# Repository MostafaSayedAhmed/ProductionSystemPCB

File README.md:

# Production System PCB
Internship final project for Embedded system track internship offered by Egypt Makes Electronics company
## Desciption
### 1- Prerequisites
Design a system that simulates a production process in a factory using the following
hardware:
• Two microcontrollers.
• LCD
• Keypad
• Temperature Sensor
• LDR Sensor
• Fan
### 2- System Description:

Design a multi-function machine that can do the following using modes with only one
switch to switch between the modes of operation.
To Enter the operation mode, the user must Enter his password first [1,2,3,4]
Then using a single switch, the user can switch between the following modes as follow:
The first press on the switch → will go to Mode A
The second press on the switch → will go to mode B
The third press on the switch → will go to mode B
<dl>
  <dt>Mode A: ‘Calculator’</dt>
  <ds>
On Microcontroller 1: ‘
Implement a calculator, Numbers should be from 0 to 9, and the operation is (+ -
\* / )
Display on the first MCU LCD.
</ds>
  <dt>Mode B: ‘Alarm System’</dt>
<ds>On Microcontroller 1:
User need an alarm system for a server room, A led toggle every 1 sec “flashing”,
and the value of the temp. sensor control the flashing of the led.
<ul>
<li> if the value increased than 50c:
  <ul>
    <li>
 The led will be flash every 100msec, buzzer will on and off every
100 msec
    </li>
    <li>
Send Signal to Microcontroller 2 to move the motor in CW
direction with maximum speed. Using any communication
protocol (i.e. UART)
  </li>
  </ul>
  </li>
<li>
 If the value is lower than 50c:
  <ul>
  <li>
The led will be flash every 1 sec, buzzer and motor are turned
off.
</li>
  <li>
 Send Signal to Microcontroller 2 to move the motor in CCW
direction with half speed. Using any communication protocol
(i.e. UART)
On Microcontroller 2:
Controller the motor speed according to the received signal

</li>
</li>
</ul></ul>
</ds>
<dt>Mode C: ‘Sun light indication’ </dt>
<ds>
  On Microcontroller 2
<ul>
<li>if LDR detect the high amount of light:
The Led will turned off and the second MCU will send txt to be print on
LCD “Morning” of the first MCU through UART. </li>
  <li>if LDR detect the Low amount of light:
The led will turned on and the second MCU will send txt to be print on LCD
“Night” of the first MCU through UART.</li>
</ul>
</ds>
</dt>

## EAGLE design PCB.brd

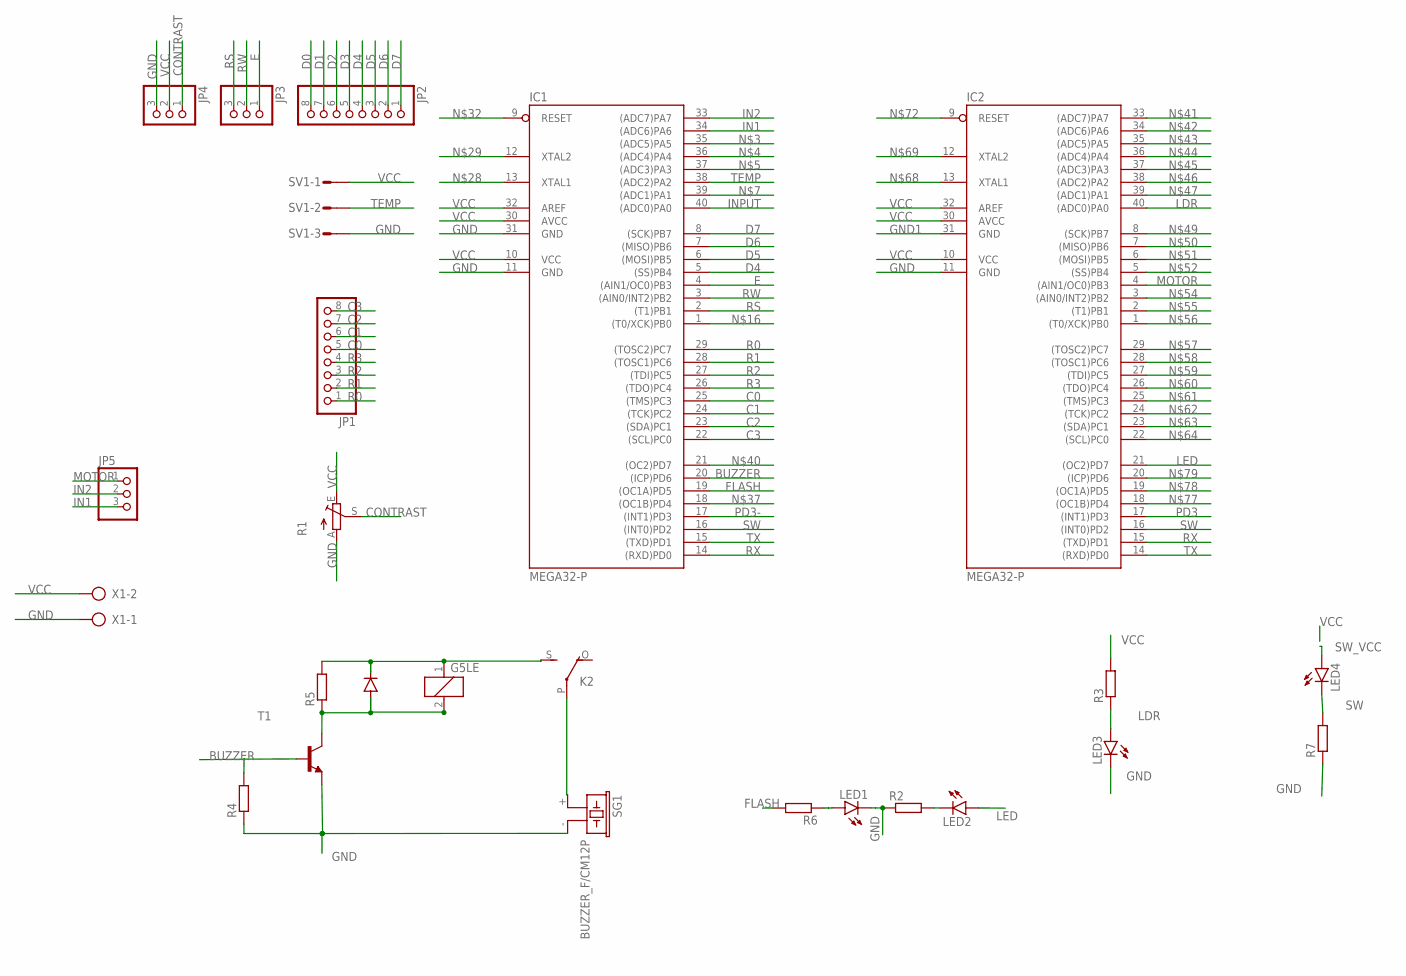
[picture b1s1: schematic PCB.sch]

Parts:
D1: 1N4004; DO41-10
IC1, IC2: MEGA32-P; DIL40
JP1, JP2: PINHD-1X8; 1X08
JP3, JP4, JP5: PINHD-1X3; 1X03
K2: G5LE
LED1, LED2: LED3MM
LED3, LED4: LED5MM
R1: TRIM_EU-RJ9W; RJ9W
R2, R3, R4, R5, R6, R7: R-EU_0204/7; 0204/7
SG1: BUZZER_F/CM12P
SV1: CON-AMP-MT_S03P
T1: 2N2222-NPN-TO92-EBC; TO92-EBC
X1: CON-PTR500_AK300/2

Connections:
BUZZER: IC1.20 ((ICP)PD6)
C0: IC1.25 ((TMS)PC3), JP1.5
C1: IC1.24 ((TCK)PC2), JP1.6
C2: IC1.23 ((SDA)PC1), JP1.7
C3: IC1.22 ((SCL)PC0), JP1.8
CONTRAST: JP4.1, R1.S
D0: JP2.8
D1: JP2.7
D2: JP2.6
D3: JP2.5
D4: IC1.5 ((SS)PB4), JP2.4
D5: IC1.6 ((MOSI)PB5), JP2.3
D6: IC1.7 ((MISO)PB6), JP2.2
D7: IC1.8 ((SCK)PB7), JP2.1
E: IC1.4 ((AIN1/OC0)PB3), JP3.1
FLASH: IC1.19 ((OC1A)PD5), R6.2
GND: IC1.11 (GND), IC1.31 (GND), IC2.11 (GND), JP4.3, LED1.K (C), LED3.K (C), R1.A, R2.1, R4.1, R7.1, SG1.- (2), SV1.3, T1.E, X1.1
GND1: IC2.31 (GND)
IN1: IC1.34 ((ADC6)PA6), JP5.3
IN2: IC1.33 ((ADC7)PA7), JP5.2
INPUT: IC1.40 ((ADC0)PA0)
LDR: IC2.40 ((ADC0)PA0), LED3.A, R3.1
LED: IC2.21 ((OC2)PD7), LED2.A
MOTOR: IC2.4 ((AIN1/OC0)PB3), JP5.1
unnamed: K2.P, SG1.+ (1)
unnamed: D1.C, K2.1, K2.S, R5.2
unnamed: LED2.K (C), R2.2
unnamed: LED1.A, R6.1
unnamed: D1.A, K2.2, R5.1, T1.C
unnamed: R4.2, T1.B
PD3: IC2.17 ((INT1)PD3)
PD3-: IC1.17 ((INT1)PD3)
R0: IC1.29 ((TOSC2)PC7), JP1.1
R1: IC1.28 ((TOSC1)PC6), JP1.2
R2: IC1.27 ((TDI)PC5), JP1.3
R3: IC1.26 ((TDO)PC4), JP1.4
RS: IC1.2 ((T1)PB1), JP3.3
RW: IC1.3 ((AIN0/INT2)PB2), JP3.2
RX: IC1.14 ((RXD)PD0), IC2.15 ((TXD)PD1)
SW: IC1.16 ((INT0)PD2), IC2.16 ((INT0)PD2), LED4.K (C), R7.2
SW_VCC: LED4.A
TEMP: IC1.38 ((ADC2)PA2), SV1.2
TX: IC1.15 ((TXD)PD1), IC2.14 ((RXD)PD0)
VCC: IC1.10 (VCC), IC1.30 (AVCC), IC1.32 (AREF), IC2.10 (VCC), IC2.30 (AVCC), IC2.32 (AREF), JP4.2, R1.E, R3.2, SV1.1, X1.2

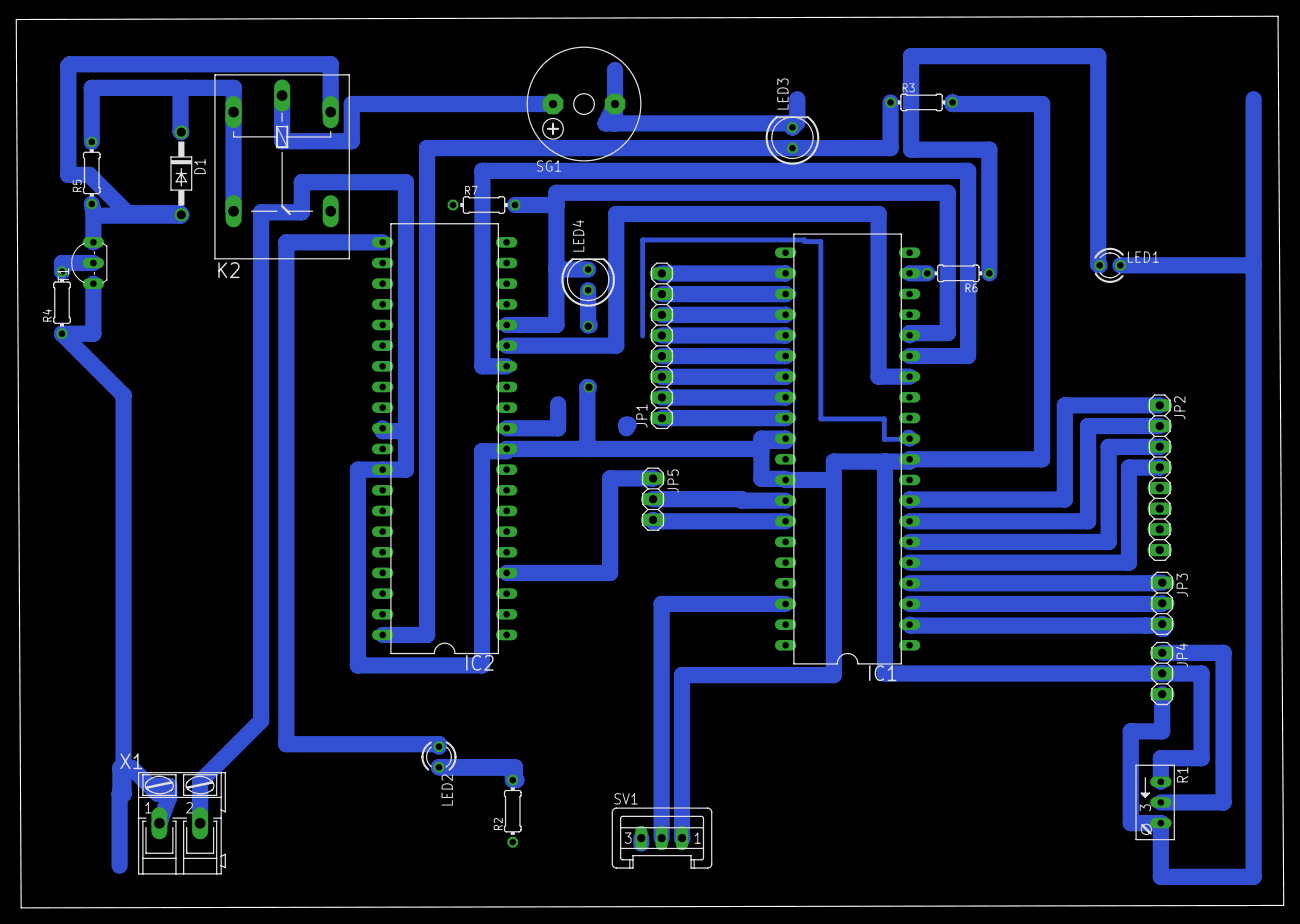
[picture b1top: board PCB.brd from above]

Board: 2 copper layers, 155.8 x 109.6 mm, 24 parts (0 on the bottom side), 34 nets.
